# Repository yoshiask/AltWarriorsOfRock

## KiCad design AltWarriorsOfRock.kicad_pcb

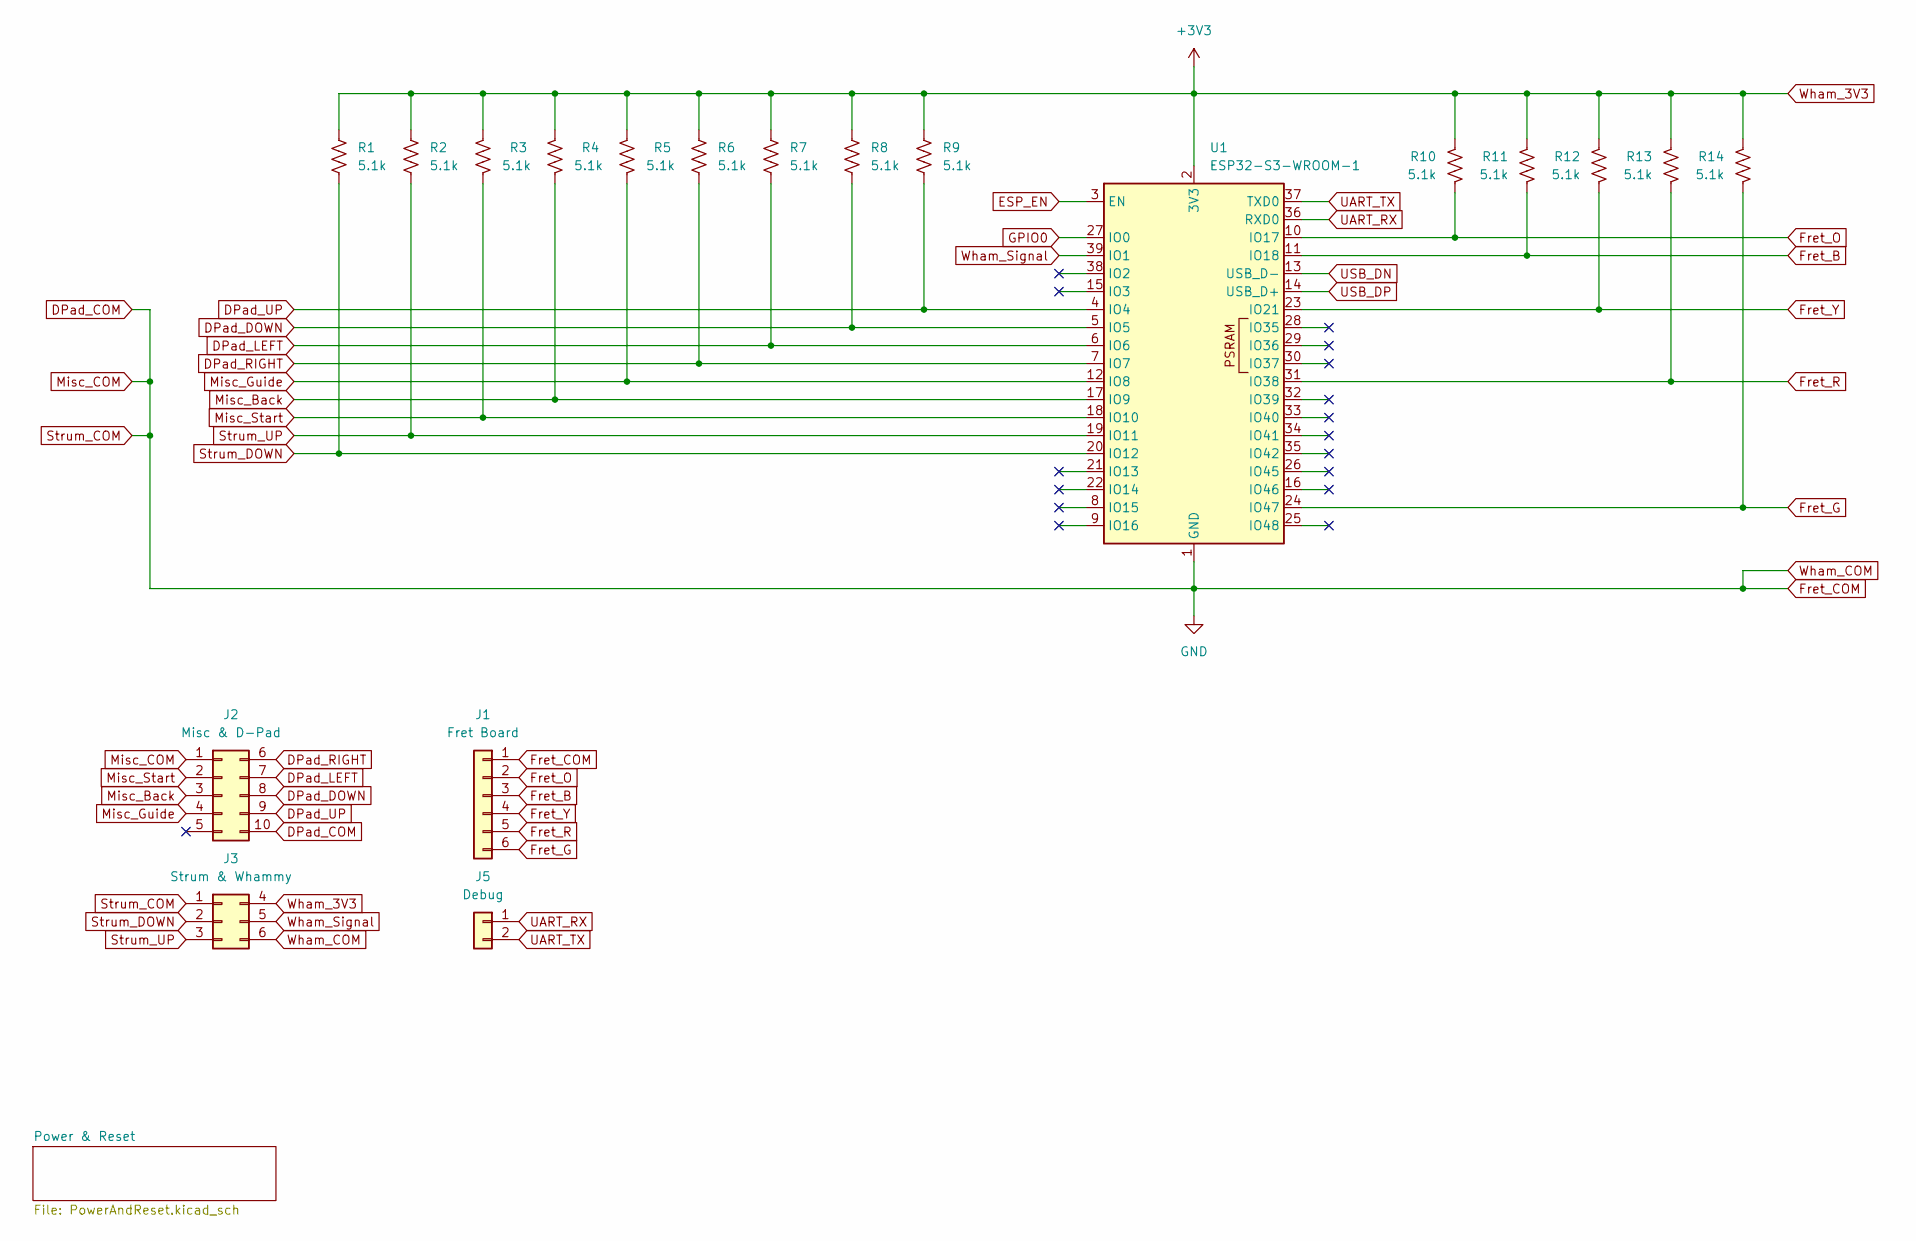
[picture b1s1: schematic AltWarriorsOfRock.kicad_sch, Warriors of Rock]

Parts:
J1: Fret Board; PinHeader_1x06_P2.54mm_Vertical
J2: Misc & D-Pad; PinHeader_2x05_P2.54mm_Vertical_TopBottom
J3: Strum & Whammy; PinHeader_2x03_P2.54mm_Vertical_TopBottom
J5: Debug; PinHeader_1x02_P2.54mm_Vertical
R1, R2, R3, R4, R5, R6, R7, R8, R9, R10, R11, R12, R13, R14: 5.1k; R_1206_3216Metric_Pad1.30x1.75mm_HandSolder
U1: ESP32-S3-WROOM-1

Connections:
DPad_COM: J1.1, J2.1, J2.10, J3.1, J3.6, U1.1 (GND), U1.40 (GND), U1.41 (GND); also elsewhere on the board
DPad_DOWN: J2.8, R8.2, U1.5 (IO5)
DPad_LEFT: J2.7, R7.2, U1.6 (IO6)
DPad_RIGHT: J2.6, R6.2, U1.7 (IO7)
DPad_UP: J2.9, R9.2, U1.4 (IO4)
ESP_EN: U1.3 (EN); also elsewhere on the board
Fret_B: J1.3, R11.2, U1.11 (IO18)
Fret_G: J1.6, R14.2, U1.24 (IO47)
Fret_O: J1.2, R10.2, U1.10 (IO17)
Fret_R: J1.5, R13.2, U1.31 (IO38)
Fret_Y: J1.4, R12.2, U1.23 (IO21)
GPIO0: U1.27 (IO0); also elsewhere on the board
Misc_Back: J2.3, R4.2, U1.17 (IO9)
Misc_Guide: J2.4, R5.2, U1.12 (IO8)
Misc_Start: J2.2, R3.2, U1.18 (IO10)
Strum_DOWN: J3.2, R1.2, U1.20 (IO12)
Strum_UP: J3.3, R2.2, U1.19 (IO11)
UART_RX: J5.1, U1.36 (RXD0)
UART_TX: J5.2, U1.37 (TXD0)
USB_DN: U1.13 (USB_D-); also elsewhere on the board
USB_DP: U1.14 (USB_D+); also elsewhere on the board
Wham_3V3: J3.4, R1.1, R2.1, R3.1, R4.1, R5.1, R6.1, R7.1, R8.1, R9.1, R10.1, R11.1, R12.1, R13.1, R14.1, U1.2 (3V3); also elsewhere on the board
Wham_Signal: J3.5, U1.39 (IO1)

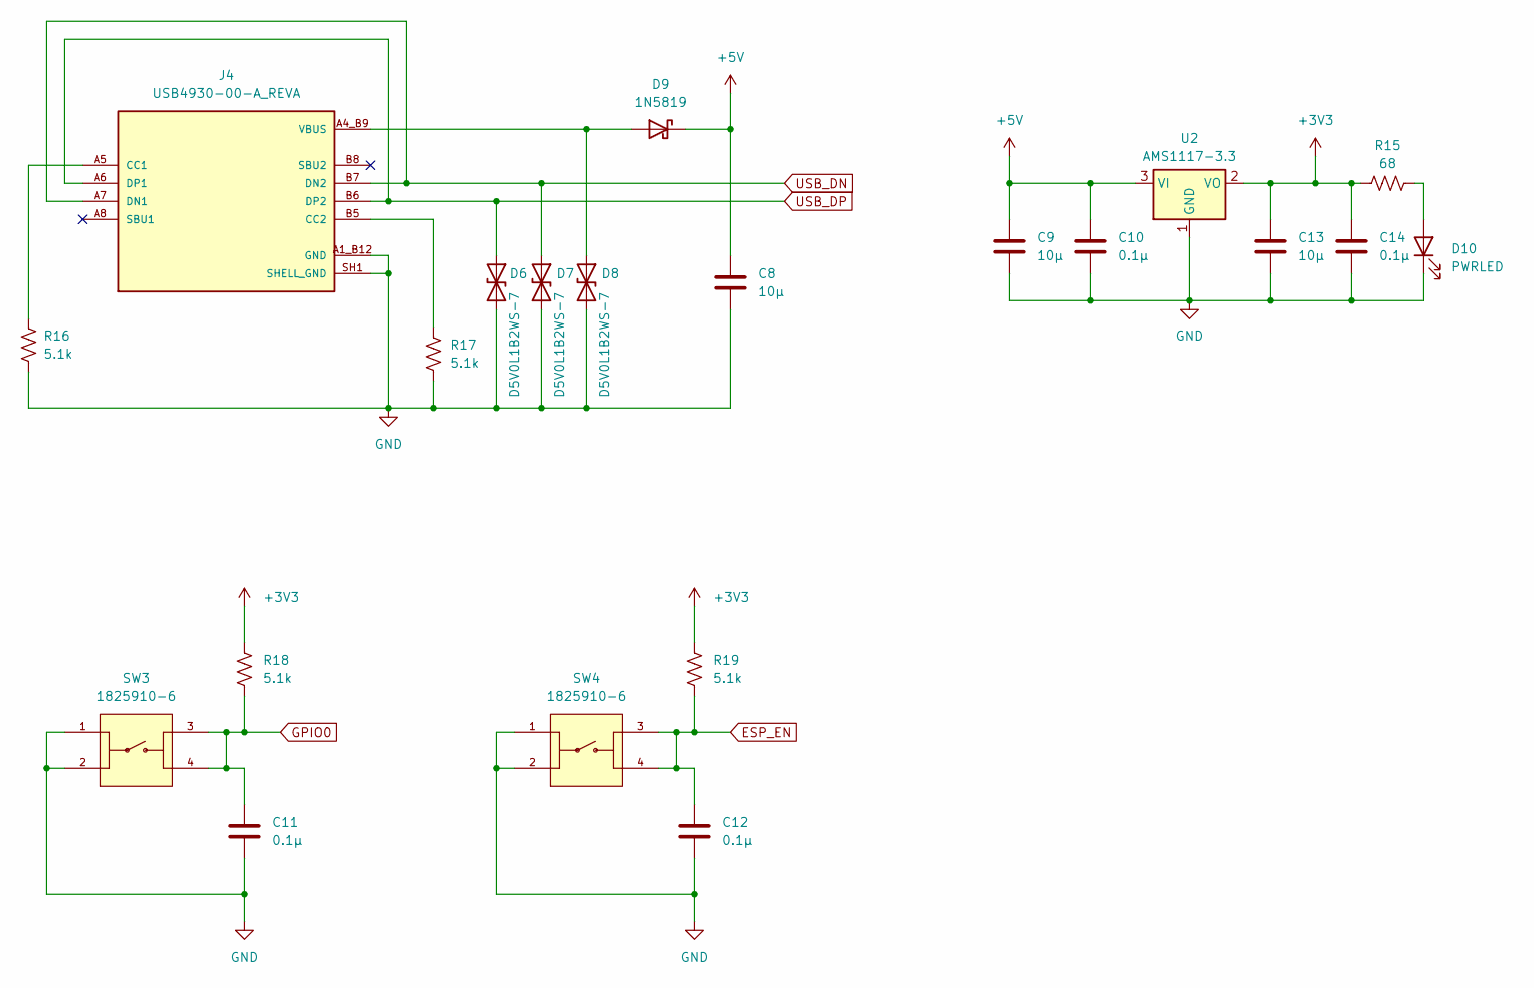
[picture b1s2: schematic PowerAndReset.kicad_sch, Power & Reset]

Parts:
C8, C9, C13: 10μ; C_0805_2012Metric_Pad1.18x1.45mm_HandSolder
C10, C11, C12, C14: 0.1μ; C_0402_1005Metric_Pad0.74x0.62mm_HandSolder
D6, D7, D8: D5V0L1B2WS-7; D_SOD-323_HandSoldering
D9: 1N5819; D_SOD-123
D10: PWRLED; LED_D3.0mm
J4: USB4930-00-A_REVA; GCT_USB4930-00-A_REVA; PARTREV A; DigiKey_Part_Number 2073-USB4930-00-ACT-ND
R15: 68; R_Axial_DIN0207_L6.3mm_D2.5mm_P10.16mm_Horizontal
R16, R17, R18, R19: 5.1k; R_1206_3216Metric_Pad1.30x1.75mm_HandSolder
SW3, SW4: 1825910-6; SW_1825910-6-4; PARTREV C10
U2: AMS1117-3.3; SOT-223-3_TabPin2

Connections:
+5V: C8.1, C9.1, C10.1, D9.1 (K), U2.3 (VI)
DPad_COM: C8.2, C9.2, C10.2, C11.2, C12.2, C13.2, C14.2, D6.2 (A2), D7.2 (A2), D8.2 (A2), D10.1 (K), J4.A1_B12 (GND), J4.B1_A12 (GND), J4.SH1 (SHELL_GND), J4.SH2 (SHELL_GND), J4.SH3 (SHELL_GND), J4.SH4 (SHELL_GND), R16.2, R17.2, SW3.1, SW3.2, SW4.1, SW4.2, U2.1 (GND); also elsewhere on the board
ESP_EN: C12.1, R19.2, SW4.3, SW4.4; also elsewhere on the board
GPIO0: C11.1, R18.2, SW3.3, SW3.4; also elsewhere on the board
unnamed: D10.2 (A), R15.2
unnamed: J4.A5 (CC1), R16.1
unnamed: J4.B5 (CC2), R17.1
USB_DN: D7.1 (A1), J4.A7 (DN1), J4.B7 (DN2); also elsewhere on the board
USB_DP: D6.1 (A1), J4.A6 (DP1), J4.B6 (DP2); also elsewhere on the board
VBUS: D8.1 (A1), D9.2 (A), J4.A4_B9 (VBUS), J4.B4_A9 (VBUS)
Wham_3V3: C13.1, C14.1, R15.1, R18.1, R19.1, U2.2 (VO); also elsewhere on the board

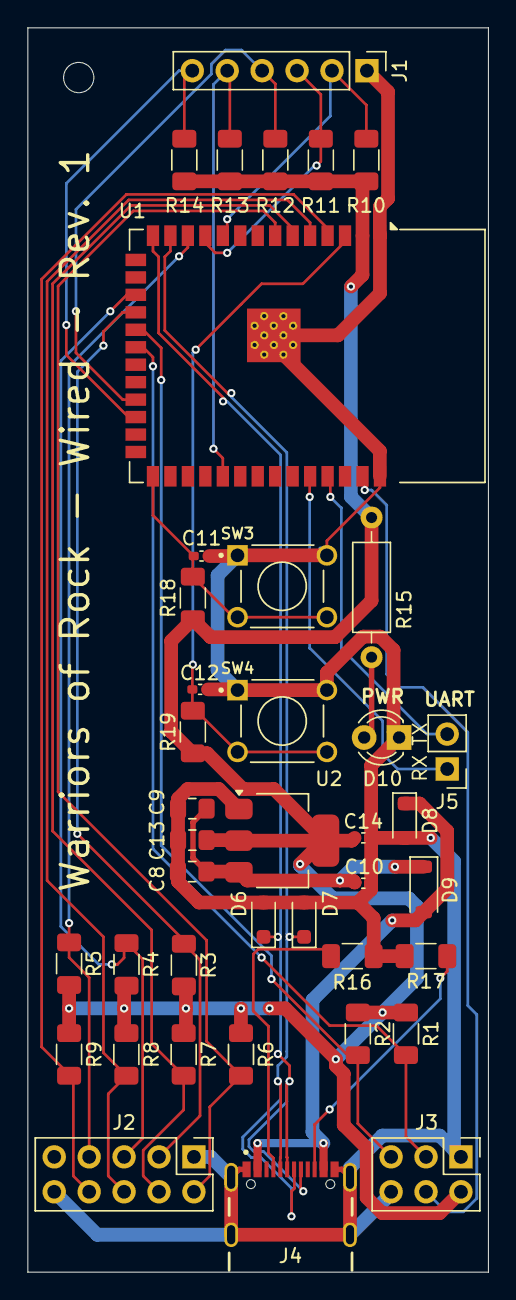
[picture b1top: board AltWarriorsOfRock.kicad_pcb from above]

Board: 2 copper layers, 33.5 x 90.5 mm, 40 parts (0 on the bottom side), 28 nets.

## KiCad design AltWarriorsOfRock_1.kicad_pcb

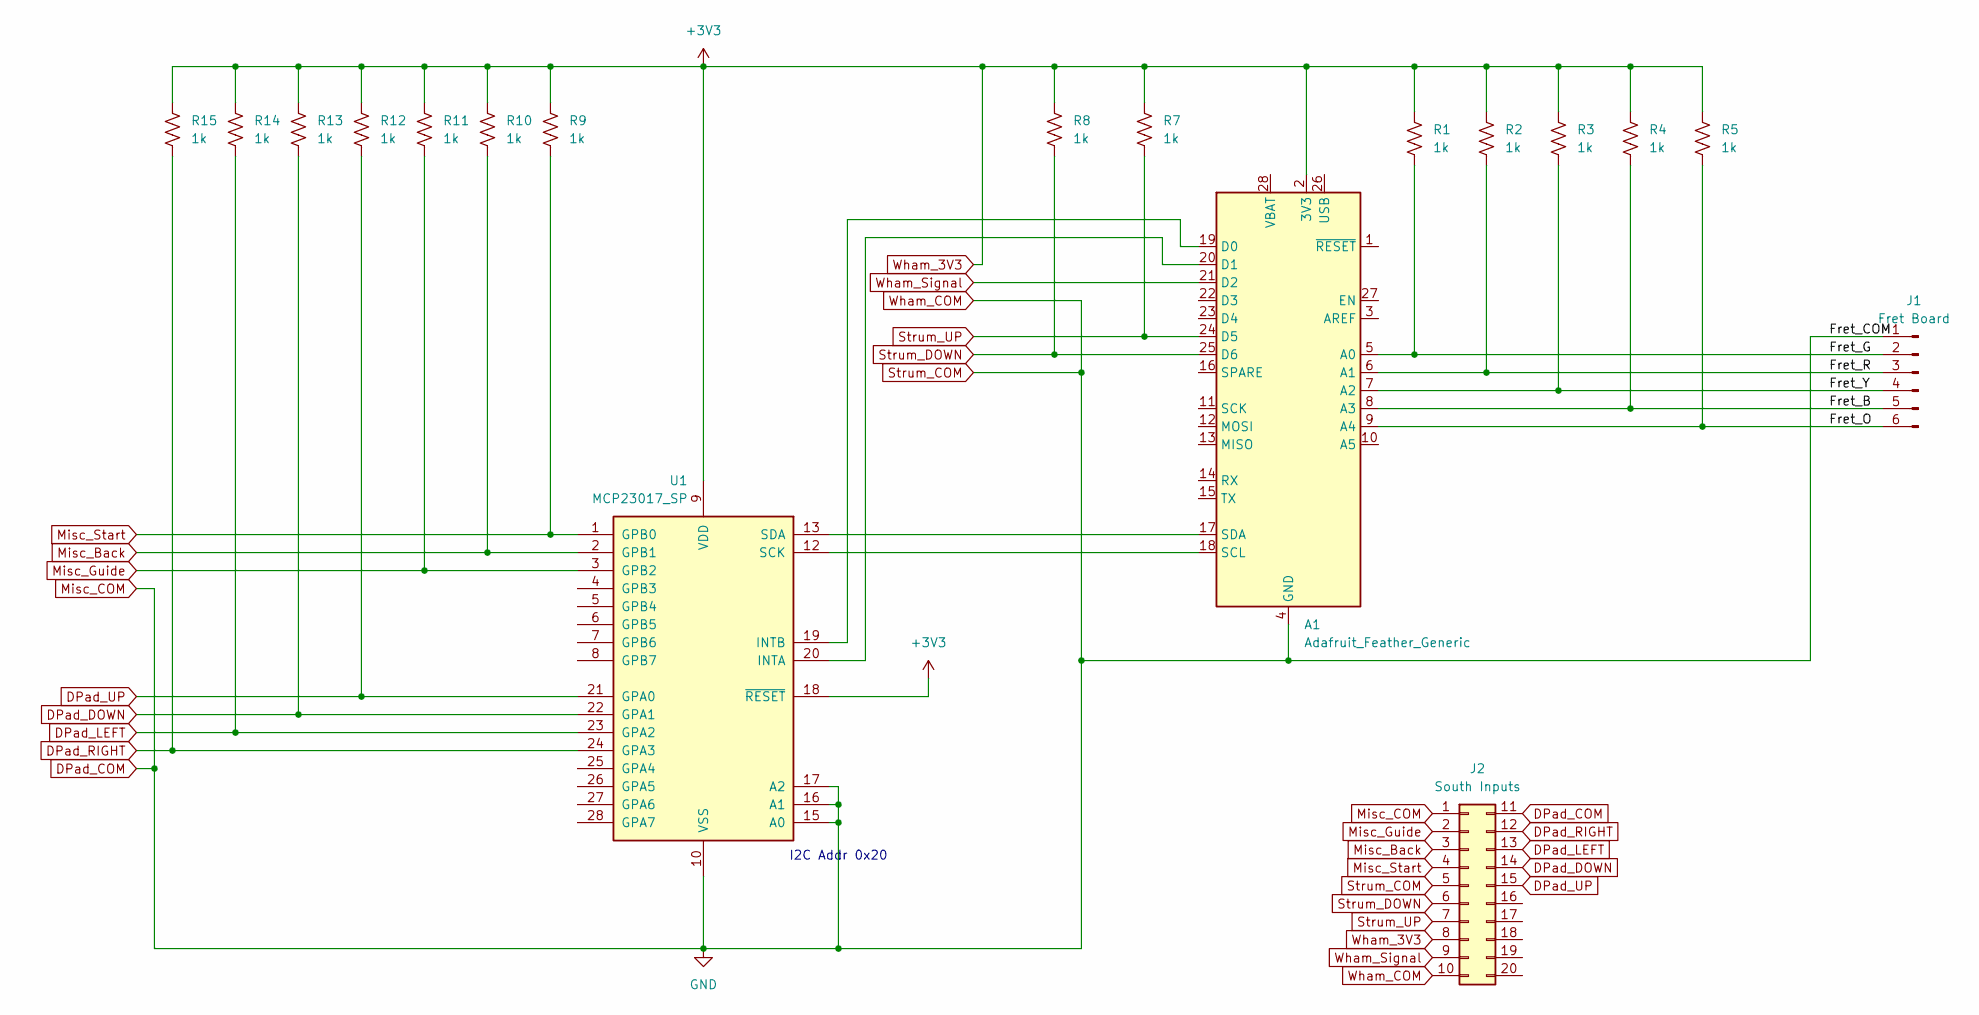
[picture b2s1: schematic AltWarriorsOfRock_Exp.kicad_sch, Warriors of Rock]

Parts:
A1: Adafruit_Feather_Generic; Adafruit_Feather
J1: Fret Board; PinHeader_1x06_P2.54mm_Vertical
J2: South Inputs; PinHeader_2x10_P2.54mm_Vertical_TopBottom
R1, R2, R3, R4, R5, R7, R8, R9, R10, R11, R12, R13, R14, R15: 1k; R_Axial_DIN0204_L3.6mm_D1.6mm_P7.62mm_Horizontal
U1: MCP23017_SP; DIP-28_W7.62mm

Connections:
/Fret_B: A1.8 (A3), J1.5, R4.2
/Fret_G: A1.5 (A0), J1.2, R1.2
/Fret_O: A1.9 (A4), J1.6, R5.2
/Fret_R: A1.6 (A1), J1.3, R2.2
/Fret_Y: A1.7 (A2), J1.4, R3.2
DPad_COM: A1.4 (GND), J1.1, J2.1, J2.5, J2.10, J2.11, U1.10 (VSS), U1.15 (A0), U1.16 (A1), U1.17 (A2)
DPad_DOWN: J2.14, R13.2, U1.22 (GPA1)
DPad_LEFT: J2.13, R14.2, U1.23 (GPA2)
DPad_RIGHT: J2.12, R15.2, U1.24 (GPA3)
DPad_UP: J2.15, R12.2, U1.21 (GPA0)
Misc_Back: J2.3, R10.2, U1.2 (GPB1)
Misc_Guide: J2.2, R11.2, U1.3 (GPB2)
Misc_Start: J2.4, R9.2, U1.1 (GPB0)
unnamed: A1.19 (D0), U1.19 (INTB)
unnamed: A1.20 (D1), U1.20 (INTA)
unnamed: A1.18 (SCL), U1.12 (SCK)
unnamed: A1.17 (SDA), U1.13 (SDA)
Strum_DOWN: A1.25 (D6), J2.6, R8.2
Strum_UP: A1.24 (D5), J2.7, R7.2
Wham_3V3: A1.2 (3V3), J2.8, R1.1, R2.1, R3.1, R4.1, R5.1, R7.1, R8.1, R9.1, R10.1, R11.1, R12.1, R13.1, R14.1, R15.1, U1.9 (VDD), U1.18 (~RESET)
Wham_Signal: A1.21 (D2), J2.9

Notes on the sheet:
I2C Addr 0x20

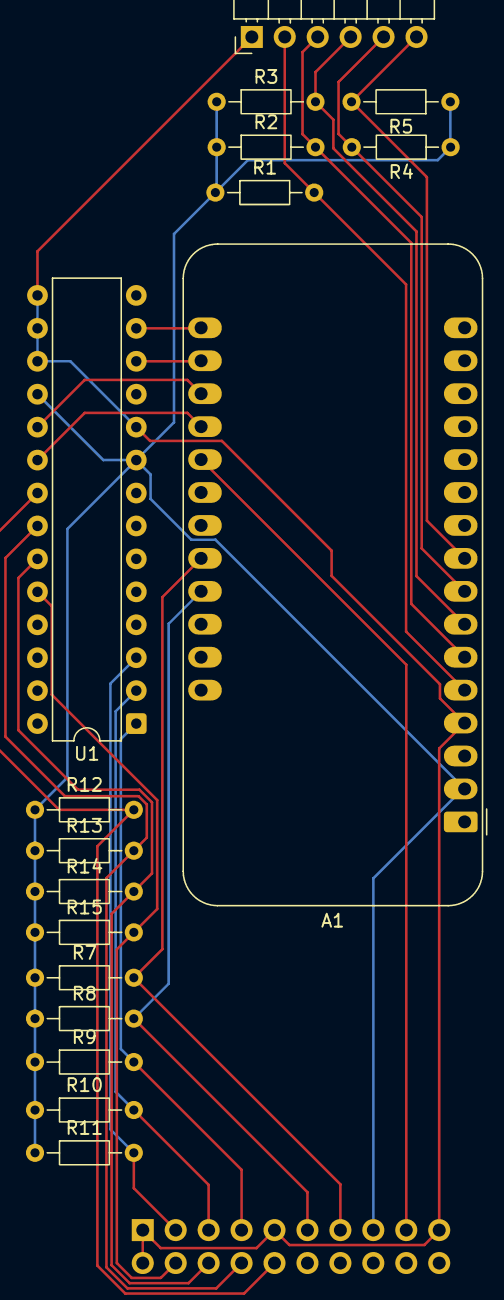
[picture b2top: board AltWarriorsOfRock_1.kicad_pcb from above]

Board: 2 copper layers, 18 parts (1 on the bottom side), 21 nets.

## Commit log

2026-02-10 Initial completed revision
2026-04-28 Switch to ESP32-S3-WROOM-1 module; Use 5.1k for all pullups
2026-04-29 Draft 01 of PCB with WROOM module
2026-04-29 [WIP] Use surface-mount headers for south headers
2026-04-30 Redo layout with USB-C port on the underside
2026-04-30 Redo layout with all components topside
2026-05-01 Update Gerbers
2026-05-01 Adjust schematic 'no connect' symbols to prevent overlap
2026-05-02 Move C10, C14 closer to respective signals; thickened power/ground traces
